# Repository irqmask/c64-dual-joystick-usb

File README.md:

# c64-dual-joystick-usb

Adapter to connect C64 joysticks to a "modern" USB port

Just connect it to the PC over a USB 1.1 port and have two joystick ports available.

This c64-dual-joystick-usb HW and SW is licensed under the GNU General Public License Version 2 GPLv2.

## Hardware

The PCB has been designed using Kicad and it is located in the 'hw' folder. This is the schematic for this little device:
<a href="https://github.com/irqmask/c64-dual-joystick-usb/blob/main/hw/c64-dual-joystick-usb.pdf">'C64 Dual Joystick USB adapter Schematic'</a>

## Firmware

The firmware for the device along with some test-firmware is located in the 'sw' folder. Build instructions: <a href="https://github.com/irqmask/c64-dual-joystick-usb/blob/main/doc/build.md">'doc/build.md'</a>

This project makes use of the v-usb library which provides low-speed USB capability for AVR microcontrollers. 
https://www.obdev.at/vusb/

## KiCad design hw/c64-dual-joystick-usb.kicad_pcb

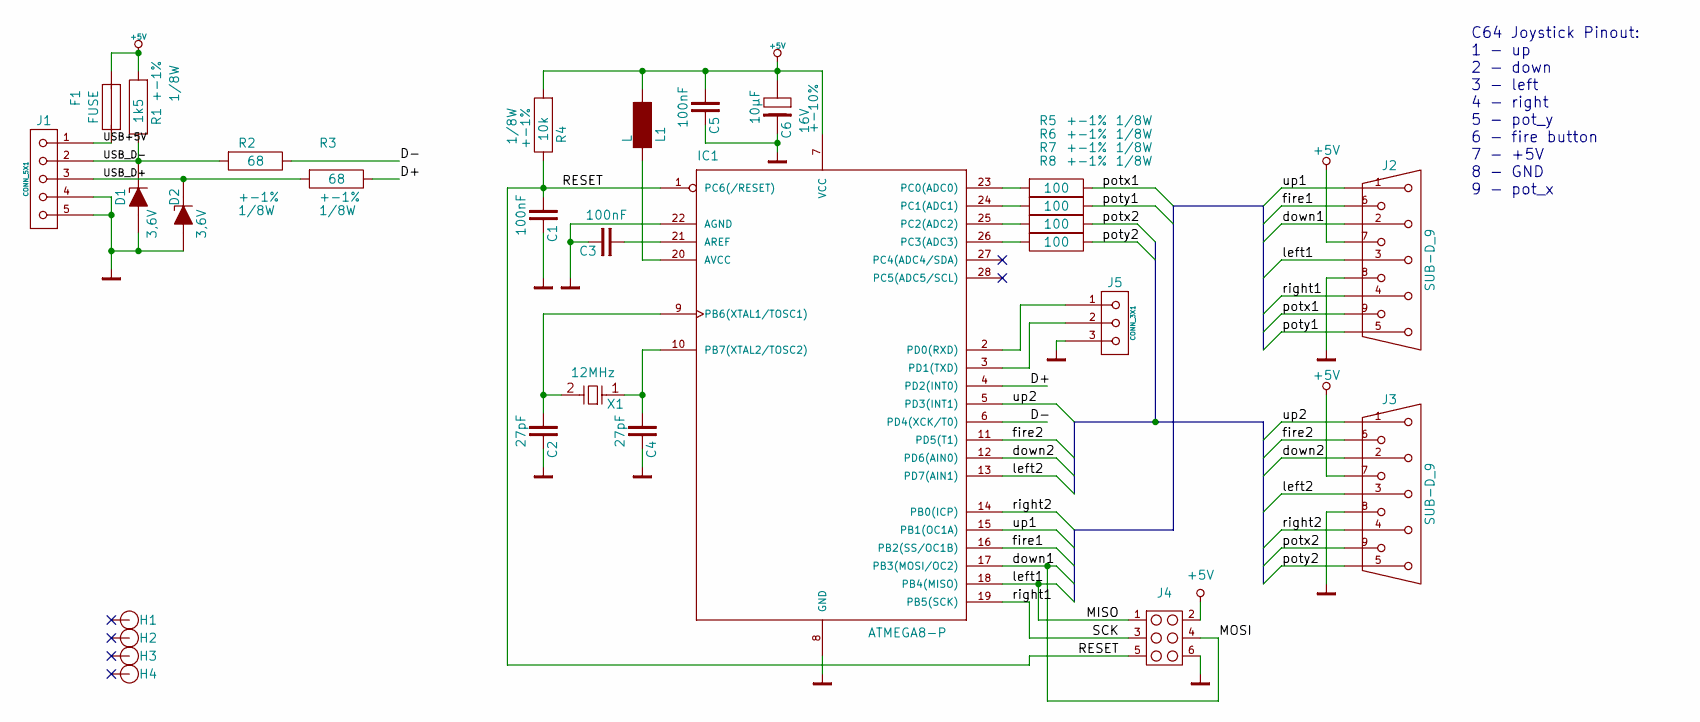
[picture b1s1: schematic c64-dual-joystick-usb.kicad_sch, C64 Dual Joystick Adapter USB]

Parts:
C1, C3, C5: 100nF
C2, C4: 27pF
C6: 10µF; Voltage 16V
D1, D2: 3,6V
F1: FUSE
H1, H2, H3, H4: HOLE
IC1: ATMEGA8-P; DIL28
J1: CONN_5X1
J2, J3: SUB-D_9
J4: CONN_3X2
J5: CONN_3X1
L1: L
R1: 1k5; Tolerance +-1%
R2, R3: 68; Tolerance +-1%
R4: 10k; Tolerance +-1%
R5, R6, R7, R8: 100; Tolerance +-1%
X1: 12MHz

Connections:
+5V: C5.1, C6.1, F1.1, IC1.7 (VCC), J2.7, J3.7, J4.2, L1.2, R1.1, R4.1; also elsewhere on the board
/D+: IC1.4 (PD2(INT0)), R3.2
/D-: IC1.6 (PD4(XCK/T0)), R2.2
/MISO: IC1.18 (PB4(MISO)), J2.3, J4.1
/MOSI: IC1.17 (PB3(MOSI/OC2)), J2.2, J4.4
/RESET: C1.1, IC1.1 (PC6(/RESET)), J4.5, R4.2
/SCK: IC1.19 (PB5(SCK)), J2.4, J4.3
/USB+5V: F1.2, J1.1
/USB_D+: D2.2 (C), J1.3, R3.1
/USB_D-: D1.2 (C), J1.2, R1.2, R2.1
/down2: IC1.12 (PD6(AIN0)), J3.2
/fire1: IC1.16 (PB2(SS/OC1B)), J2.6
/fire2: IC1.11 (PD5(T1)), J3.6
/left2: IC1.13 (PD7(AIN1)), J3.3
/potx1: J2.9, R5.2
/potx2: J3.9, R7.2
/poty1: J2.5, R6.2
/poty2: J3.5, R8.2
/right2: IC1.14 (PB0(ICP)), J3.4
/up1: IC1.15 (PB1(OC1A)), J2.1
/up2: IC1.5 (PD3(INT1)), J3.1
GND: C1.2, C2.2, C3.2, C4.2, C5.2, C6.2, D1.1 (A), D2.1 (A), IC1.8 (GND), IC1.22 (AGND), J1.4, J1.5, J2.8, J3.8, J4.6, J5.3
unnamed: IC1.23 (PC0(ADC0)), R5.1
unnamed: IC1.26 (PC3(ADC3)), R8.1
unnamed: IC1.24 (PC1(ADC1)), R6.1
unnamed: C3.1, IC1.21 (AREF)
unnamed: C4.1, IC1.10 (PB7(XTAL2/TOSC2)), X1.1
unnamed: IC1.2 (PD0(RXD)), J5.1
unnamed: IC1.3 (PD1(TXD)), J5.2
unnamed: IC1.25 (PC2(ADC2)), R7.1
unnamed: C2.1, IC1.9 (PB6(XTAL1/TOSC1)), X1.2
unnamed: IC1.20 (AVCC), L1.1

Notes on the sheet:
C64 Joystick Pinout: 1 - up 2 - down 3 - left 4 - right 5 - pot_y 6 - fire button 7 - +5V 8 - GND 9 - pot_x

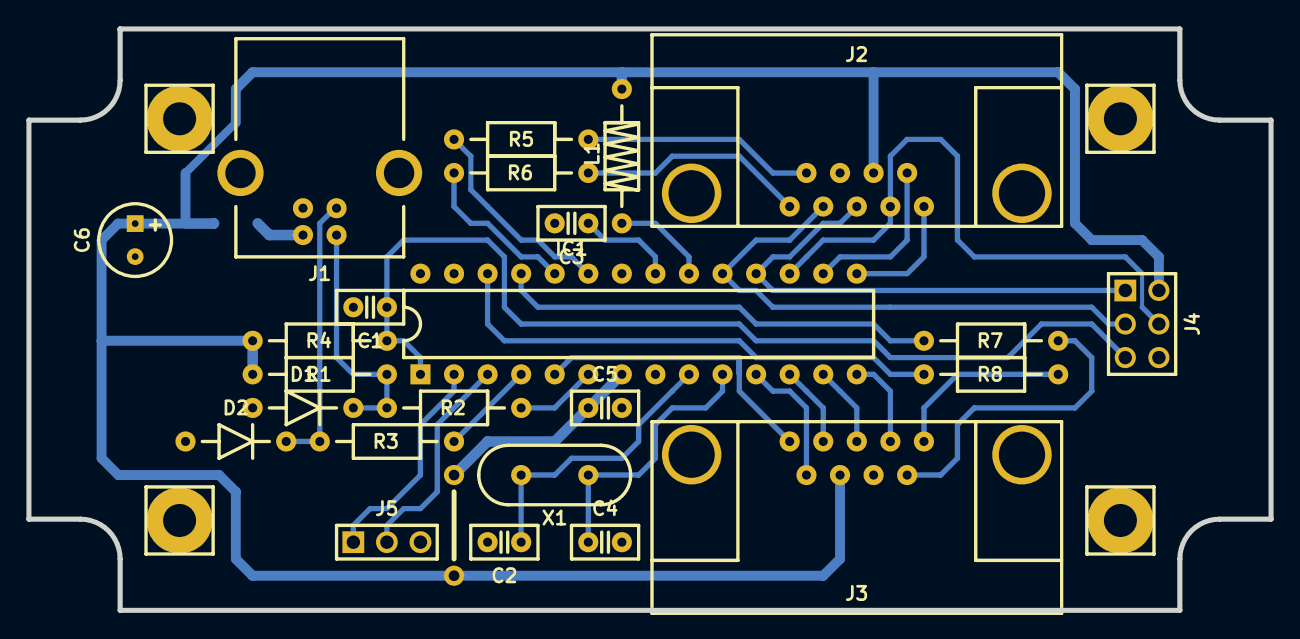
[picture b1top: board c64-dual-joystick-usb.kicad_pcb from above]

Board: 2 copper layers, 94.0 x 44.0 mm, 30 parts (1 on the bottom side), 32 nets.

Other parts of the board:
WIRE300: VAL**; WIRE300

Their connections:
+5V: WIRE300.1; also elsewhere on the board

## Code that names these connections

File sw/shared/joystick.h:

/**
 * @file joystick.h
 */

#ifndef JOYSTICK_H_
#define JOYSTICK_H_

// --- Include section ---------------------------------------------------------

#include <stdbool.h>

// --- Definitions -------------------------------------------------------------

#define JOY1_UP_PIN     PINB
#define JOY1_UP_BIT     PB1
#define JOY1_DOWN_PIN   PINB
#define JOY1_DOWN_BIT   PB3
#define JOY1_LEFT_PIN   PINB
#define JOY1_LEFT_BIT   PB4
#define JOY1_RIGHT_PIN  PINB
#define JOY1_RIGHT_BIT  PB5
#define JOY1_FIRE_PIN   PINB
#define JOY1_FIRE_BIT   PB2

#define JOY1_PORTB_MASK ((1<<PB1) | (1<<PB2) | (1<<PB3) | (1<<PB4) | (1<<PB5))
#define JOY1_PORTD_MASK 0

#define JOY2_UP_PIN     PIND
#define JOY2_UP_BIT     PD3
#define JOY2_DOWN_PIN   PIND
#define JOY2_DOWN_BIT   PD6
#define JOY2_LEFT_PIN   PIND
#define JOY2_LEFT_BIT   PD7
#define JOY2_RIGHT_PIN  PINB
#define JOY2_RIGHT_BIT  PB0
#define JOY2_FIRE_PIN   PIND
#define JOY2_FIRE_BIT   PD5

#define JOY2_PORTB_MASK (1<<PB0)
#define JOY2_PORTD_MASK ((1<<PD3) | (1<<PD5) | (1<<PD6) | (1<<PD7))

// --- Type definitions --------------------------------------------------------

// --- Local variables ---------------------------------------------------------

// --- Global variables --------------------------------------------------------

// --- Module global variables -------------------------------------------------

// --- Local functions ---------------------------------------------------------

// --- Module global functions -------------------------------------------------

// --- Global functions --------------------------------------------------------

void joy_init           (void);
void joy_update         (void);
bool joy_event          (uint8_t port);

bool joy_1_is_up        (void);
bool joy_1_is_down      (void);
bool joy_1_is_left      (void);
bool joy_1_is_right     (void);
bool joy_1_is_fireing   (void);

bool joy_2_is_up        (void);
bool joy_2_is_down      (void);
bool joy_2_is_left      (void);
bool joy_2_is_right     (void);
bool joy_2_is_fireing   (void);

#endif /* JOYSTICK_H_ */

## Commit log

2025-01-02 Initial version of C64 dual joystick adapter USB
2025-01-02 Simplify joystick polling
2025-01-02 Add images to project documentation. Link to build instructions.
